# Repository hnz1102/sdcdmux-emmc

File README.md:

<div align="center">
  <h1><code>SDCDMUX</code></h1>
  
</div>

# SDCDMUX : SD Card and eMMC Device Multiplexsor with Infrared Remote Control

The SDCDMUX provides a convenient and quick change of a SW image of a device that has an SD Card interface from a remote. 

When I am developing by booting from an SD memory card on a device such as the Raspberry Pi, it is not easy to rewrite the SD card image and replace it by hand. Remove the SD card, insert it into the host PC, and take a dozen minutes rewriting the SW image, after that, return the SD card to the device and turn on the power... But, This tool can change the image of the eMMC directly from the host PC, and the device can be booted as an SD card with the new image.

Usually, To boot with the new SW image, the device must be reset, but this tool can learn the ON/OFF command of the infrared power controller and outputs that command to turn the device on and off.

This tool frees me from the tedious SW image rewriting and resetting process.

https://github.com/hnz1102/sdcdmux-emmc/assets/111413646/edf4297e-6da3-4eba-aacd-01ee126e1040

### [2023.8.15] USB Type-C version Added.

The Schematic is hardware/emmc-type-c-version/ directory.

## Features

- **Fast**. SDCDMUX can write an image to the eMMC device (32GB) instead of SD Memory Card via High-Speed USB. It is 4 times faster than an SD card. 

- **Remote Control**. SDCDMUX has an infrared interface that can receive an infrared remote control command and send it to power control devices. If you want to turn on a device, you can type the command "on" on the PC console.

- **Use Fast Switch**. When I used the prototype, Sometimes Rasbery Pi4 could not boot by read error. I tried to change faster switching devices in this tool. Then, Raspberry Pi always can boot correctly.

## Tested Devices

I have checked the following devices that can boot from this tool.

- [Raspberry Pi 4 Model B](https://www.raspberrypi.com/products/raspberry-pi-4-model-b/)
- [BeagleBone Black](https://beagleboard.org/black)
- [BeagleBone Blue](https://beagleboard.org/blue)

Only 3 devices because I have my own now.

## Infrared Remote Power Switch

The Infrared Remote Contorol Power Swtich I used is [OCR-05W OHM ELECTRIC INC.](https://www.ohm-electric.co.jp/product/c23/c2313/19582/). But I think other switch devices that can control by the infrared LED may be able to work too. 

## How to build the control SW.

This software (sdcdmux) is for Linux. 

The following example is for Ubuntu Linux Ubuntu 22.04.2 LTS.

1. Install build tools
```
$ sudo apt -y install build-essential libftdi-dev
```

2. Build the software.
```
$ cd sdcdmux
$ make
$ sudo cp sdcdmux /usr/local/bin/ 
```
3. Add a udev rule.
/etc/udev/rules.d/99-ft232h.rules
```
$ sudo su
# echo 'SUBSYSTEMS=="usb", ATTRS{idVendor}=="0403", ATTRS{idProduct}=="6014",  MODE=
"0666"' > /etc/udev/rules.d/99-ft232h.rules
# udevadm control --reload-rules
# udevadm trigger
```

## How to use SDCDMUX.

1. Connect to SDCDMUX via the USB cable with your PC. Power USB cable connect to the target device and USB adoptor. Please refer to the figure. 

2. Use SDCDMUX

- Display current status.
```
$ sdcdmux
Memory Device is connected to : HOST.
```

- Capture infrared ON command.
```
$ sdcdmux -c on
Capture Start.. 
"Push ON button on your Infrared Remote Controller"
Recieve IFR data (18245B)
Captured command for on
```

After capture the command, you can see the 'if-on' file in the current directory.

- Capture infrared OFF command.
```
$ sdcdmux -c off
Capture Start.. 
"Push OFF button on your Infrared Remote Controller"
Recieve IFR data (11449B)
Captured command for off
```

- Select eMMC memory to host PC side.
```
$ sdcdmux -s host
Memory Device is connected to : HOST.
```
You can see eMMC disk drive on your PC.
```
$ lsblk
:
sdb           8:16   1  29.1G  0 disk 
:
```
In my case, I can see the new disk drive as 'sdb'.

- Download the Raspberry Pi boot image and Write it to eMMC.

** !WARNING! ** DO NOT OVERWRITE YOUR SYSTEM DISK DRIVE! BE CAREFUL THE WRITING DISK DRIVE NAME.

```
$ wget https://downloads.raspberrypi.org/raspios_armhf/images/raspios_armhf-2023-05-03/2023-05-03-raspios-bullseye-armhf.img.xz
$ xzcat 2023-05-03-raspios-bullseye-armhf.img.xz | sudo dd of=/dev/sdb bs=1M status=progress
4125163520 bytes (4.1 GB, 3.8 GiB) copied, 94 s, 43.9 MB/s
0+491118 records in
0+491118 records out
4143972352 bytes (4.1 GB, 3.9 GiB) copied, 126.121 s, 32.9 MB/s
$ lsblk
sdb           8:16   1  29.1G  0 disk 
├─sdb1        8:17   1   256M  0 part 
└─sdb2        8:18   1   3.6G  0 part 
```

- Select eMMC memory to target (Raspberry Pi) device.
```
$ sdcdmux -s target
Memory Device is connected to : TARGET.
```
You can see the blue LED is turn on.

- Turn on the device using infrared on command.
```
$ sdcdmux -x on
```

- Turn off the device using infrared on command.
```
$ sdcdmux -x off
```

- Another devices control.

I also use the SDCDMUX as a controller to turn ceiling lights on and off.
```
$ sdcdmux -c lightson
Capture Start.. 
"Press ON on the remote controller of the ceiling light to make it learn the command."
Recieve IFR data (8498B)
Captured command for lightson

$ sdcdmux -c lightsoff
Capture Start.. 
"Press OFF on the remote controller of the ceiling light to make it learn the command."
Recieve IFR data (10701B)
Captured command for lightsoff

$ sdcdmux -x lightson
"Seiling lights turn on."

$ sdcdmux -x lightsoff
"Seiling lights turn off."
```

## Performance

I created an SD card type and an eMMC type. I compared their writing times.

4.2GB Image Writing Time (Average of 3 times)
|SD card (*1)|eMMC (*2)|
|----|----|
|482.3 sec (8.7MB/s)|134.7 sec (31.3MB/s)|

*1 San Disk Ultla 32GB HC1 SD CARD

*2 Delkin Devices EM32VSUKN 32GB eMMC

## SDCDMUX Board

SDCDMUX Board Schematic and a PCB layout are placed in the hardware directory. There are 2 types emmc-version and sdcard-version. This emmc-version uses an eMMC device instead of a SD memory card.
Schematic data is created by KidCad 7.0.

If you order a PCB board from a PCB maker, it must be 0.8mm thick. Otherwise, it will not fit in the SD card slot.

After building the board, It has to configure EEPROMs of the USB Media Controller and USB FIFO Interface.

The USB Media Controller has an EEPROM. It is programmed with the parameters by [USBDM tool](https://www.microchip.com/en-us/software-library/usbdm-tool).

- Manufacture String
- Serial Number String

Single Channel HiSpeed USB to Multipurpose UART/FIFO IC (FT232H) has an EEPROM too. It is programmed the parameters by [FT_Prog](https://ftdichip.com/wp-content/uploads/2023/06/FT_Prog_v3.12.32.640-Installer.zip).

- FT EEPROM - HARDWARE Specific IO Controls - C5, C6, C8 and C9 ports are I/O Mode set.

# CASE

I created the case for SDCDMUX type-C version by 3D printer. There are STL data in the hardware/emmc-type-c-version/case directory.

## LICENSE
This Software is licensed under MIT. Other Hardware Schematic documents are licensed under CC-BY-SA V4.0.

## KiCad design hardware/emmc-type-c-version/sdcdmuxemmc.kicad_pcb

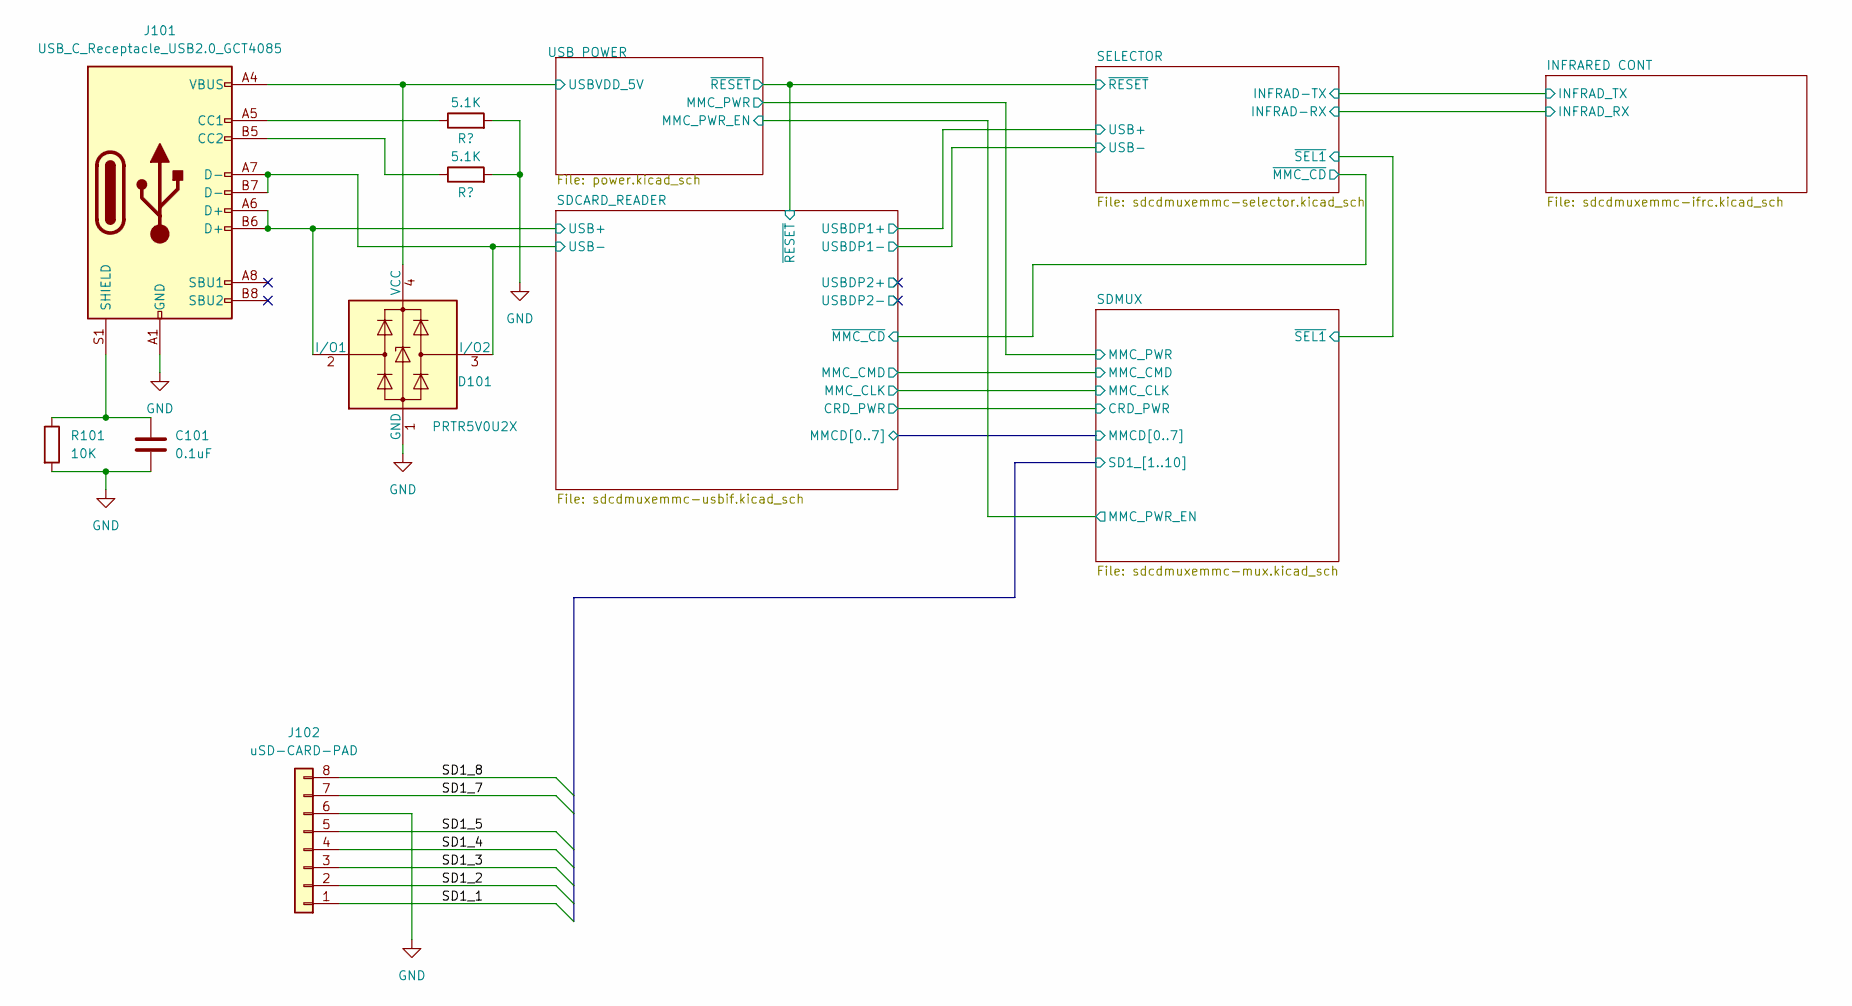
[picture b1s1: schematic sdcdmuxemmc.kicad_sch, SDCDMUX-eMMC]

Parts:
C101: 0.1uF; C_0603_1608Metric_Pad1.08x0.95mm_HandSolder; digikey 311-1824-1-ND
D101: PRTR5V0U2X; SOT-143; digikey 1727-3884-1-ND
J101: USB_C_Receptacle_USB2.0_GCT4085; USB_C_Receptacle_GCT_USB4085; digikey 2073-USB4085-GF-ACT-ND
J102: uSD-CARD-PAD; uSD Card Pad
R101: 10K; R_0805_2012Metric_Pad1.20x1.40mm_HandSolder; digikey 13-RC0603JR-1010KLCT-ND
R102, R103: 5.1K; R_0805_2012Metric_Pad1.20x1.40mm_HandSolder; digikey 13-RC0603JR-1010KLCT-ND

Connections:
/SDCARD_READER/USB+: D101.2 (I/O1), J101.A6 (D+), J101.B6 (D+); also elsewhere on the board
/SDCARD_READER/USB-: D101.3 (I/O2), J101.A7 (D-), J101.B7 (D-); also elsewhere on the board
/SDMUX/SD1_1: J102.1; also elsewhere on the board
/SDMUX/SD1_2: J102.2; also elsewhere on the board
/SDMUX/SD1_3: J102.3; also elsewhere on the board
/SDMUX/SD1_4: J102.4; also elsewhere on the board
/SDMUX/SD1_5: J102.5; also elsewhere on the board
/SDMUX/SD1_7: J102.7; also elsewhere on the board
/SDMUX/SD1_8: J102.8; also elsewhere on the board
/USB POWER/USBVDD_5V: D101.4 (VCC), J101.A4 (VBUS), J101.A9 (VBUS), J101.B4 (VBUS), J101.B9 (VBUS); also elsewhere on the board
GND: C101.2, D101.1 (GND), J101.A1 (GND), J101.A12 (GND), J101.B1 (GND), J101.B12 (GND), J102.6, R101.2, R102.2, R103.2; also elsewhere on the board
unnamed: J101.A5 (CC1), R102.1
unnamed: J101.B5 (CC2), R103.1
unnamed: C101.1, J101.S1 (SHIELD), R101.1

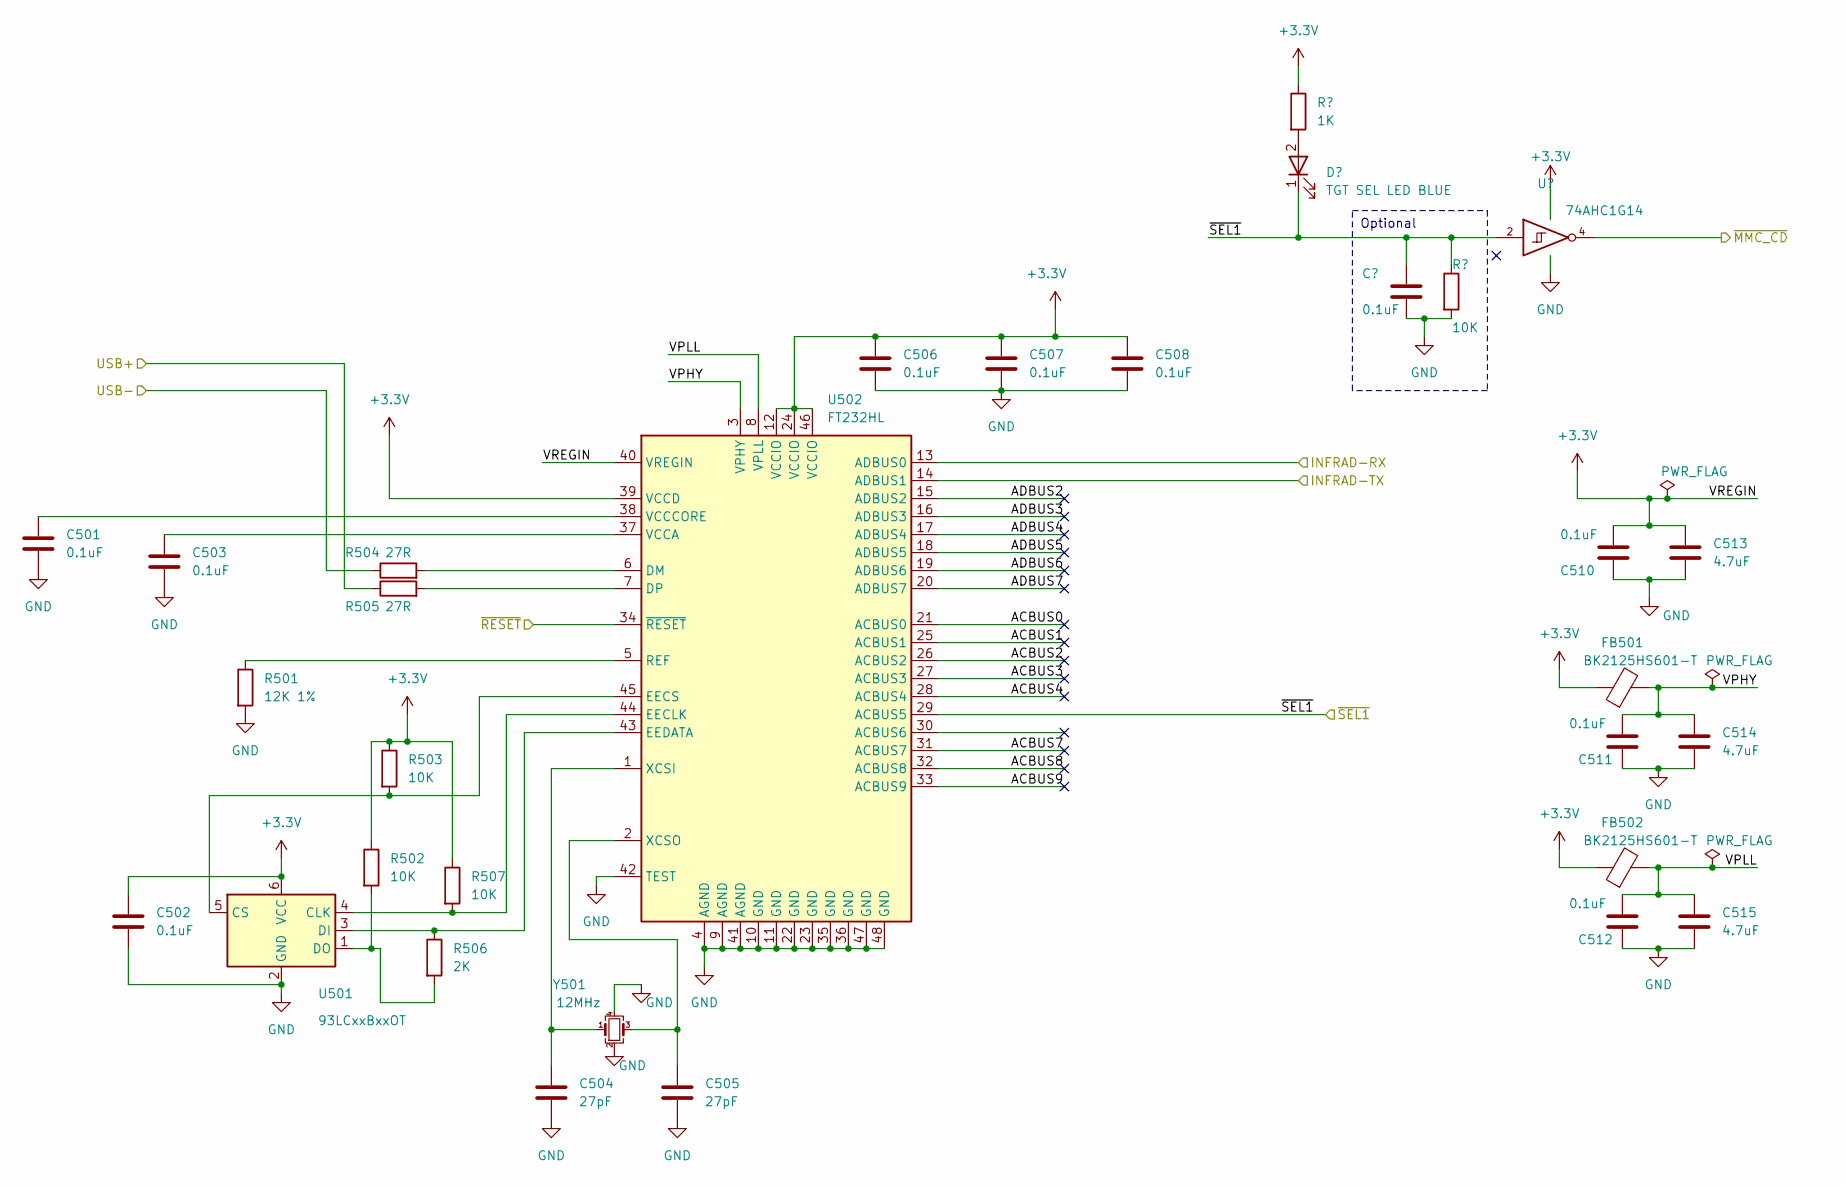
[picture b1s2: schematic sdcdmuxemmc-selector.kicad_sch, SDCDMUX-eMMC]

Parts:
C501, C502, C503, C506, C507, C508, C509, C510, C511, C512: 0.1uF; C_0603_1608Metric_Pad1.08x0.95mm_HandSolder; digikey 311-1824-1-ND
C504, C505: 27pF; C_0603_1608Metric_Pad1.08x0.95mm_HandSolder; digikey 311-1063-1-ND
C513, C514, C515: 4.7uF; C_0805_2012Metric_Pad1.18x1.45mm_HandSolder; digikey 311-1455-1-ND
D501: TGT SEL LED BLUE; LED_0603_1608Metric_Pad1.05x0.95mm_HandSolder; digikey 846-1177-1-ND
FB501, FB502: BK2125HS601-T; L_0805_2012Metric_Pad1.15x1.40mm_HandSolder; digikey 240-2399-1-ND
R501: 12K 1%; R_0805_2012Metric_Pad1.20x1.40mm_HandSolder; digikey 311-12.0KHRCT-ND
R502, R503, R507, R509: 10K; R_0805_2012Metric_Pad1.20x1.40mm_HandSolder; digikey 13-RC0603JR-1010KLCT-ND
R504, R505: 27R; R_0603_1608Metric_Pad0.98x0.95mm_HandSolder; digikey 311-27GRCT-ND
R506: 2K; R_0805_2012Metric_Pad1.20x1.40mm_HandSolder; digikey 311-2.0KGRCT-ND
R508: 1K; R_0805_2012Metric_Pad1.20x1.40mm_HandSolder; digikey 13-RC0603JR-101KLCT-ND
U501: 93LCxxBxxOT; SOT-23-6; digikey 93LC56BT-I/OTCT-ND
U502: FT232HL; LQFP-48_7x7mm_P0.5mm; digikey 768-1348-ND
U503: 74AHC1G14; SOT-23-5_HandSoldering; digikey 74AHC1G14W5-7DICT-ND
Y501: 12MHz; Crystal_SMD_3225-4Pin_3.2x2.5mm; digikey SER3682CT-ND

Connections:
+3.3V: C502.1, C506.1, C507.1, C508.1, C510.1, C513.1, FB501.1, FB502.1, R502.1, R503.1, R507.1, R508.1, U501.6 (VCC), U502.12 (VCCIO), U502.24 (VCCIO), U502.39 (VCCD), U502.40 (VREGIN), U502.46 (VCCIO), U503.5 (VCC); also elsewhere on the board
/INFRARED CONT/INFRAD_RX: U502.13 (ADBUS0); also elsewhere on the board
/INFRARED CONT/INFRAD_TX: U502.14 (ADBUS1); also elsewhere on the board
/SDCARD_READER/USBDP1+: R505.1; also elsewhere on the board
/SDCARD_READER/USBDP1-: R504.1; also elsewhere on the board
/SDCARD_READER/~MMC_CD: U503.4; also elsewhere on the board
/SDCARD_READER/~RESET: U502.34 (~RESET); also elsewhere on the board
/SELECTOR/ACBUS0: U502.21 (ACBUS0)
/SELECTOR/ACBUS1: U502.25 (ACBUS1)
/SELECTOR/ACBUS2: U502.26 (ACBUS2)
/SELECTOR/ACBUS3: U502.27 (ACBUS3)
/SELECTOR/ACBUS4: U502.28 (ACBUS4)
/SELECTOR/ACBUS7: U502.31 (ACBUS7)
/SELECTOR/ACBUS8: U502.32 (ACBUS8)
/SELECTOR/ACBUS9: U502.33 (ACBUS9)
/SELECTOR/ADBUS2: U502.15 (ADBUS2)
/SELECTOR/ADBUS3: U502.16 (ADBUS3)
/SELECTOR/ADBUS4: U502.17 (ADBUS4)
/SELECTOR/ADBUS5: U502.18 (ADBUS5)
/SELECTOR/ADBUS6: U502.19 (ADBUS6)
/SELECTOR/ADBUS7: U502.20 (ADBUS7)
/SELECTOR/VPHY: C511.1, C514.1, FB501.2, U502.3 (VPHY)
/SELECTOR/VPLL: C512.1, C515.1, FB502.2, U502.8 (VPLL)
/SELECTOR/~SEL1: C509.1, D501.1 (K), R509.1, U502.29 (ACBUS5), U503.2; also elsewhere on the board
GND: C501.2, C502.2, C503.2, C504.2, C505.2, C506.2, C507.2, C508.2, C509.2, C510.2, C511.2, C512.2, C513.2, C514.2, C515.2, R501.2, R509.2, U501.2 (GND), U502.4 (AGND), U502.9 (AGND), U502.10 (GND), U502.11 (GND), U502.22 (GND), U502.23 (GND), U502.35 (GND), U502.36 (GND), U502.41 (AGND), U502.42 (TEST), U502.47 (GND), U502.48 (GND), U503.3 (GND), Y501.2, Y501.4; also elsewhere on the board
unnamed: D501.2 (A), R508.2
unnamed: R507.2, U501.4 (CLK), U502.44 (EECLK)
unnamed: R503.2, U501.5 (CS), U502.45 (EECS)
unnamed: R506.1, U501.3 (DI), U502.43 (EEDATA)
unnamed: R502.2, R506.2, U501.1 (DO)
unnamed: R504.2, U502.6 (DM)
unnamed: R505.2, U502.7 (DP)
unnamed: R501.1, U502.5 (REF)
unnamed: C503.1, U502.37 (VCCA)
unnamed: C501.1, U502.38 (VCCCORE)
unnamed: C504.1, U502.1 (XCSI), Y501.1
unnamed: C505.1, U502.2 (XCSO), Y501.3

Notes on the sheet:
Optional

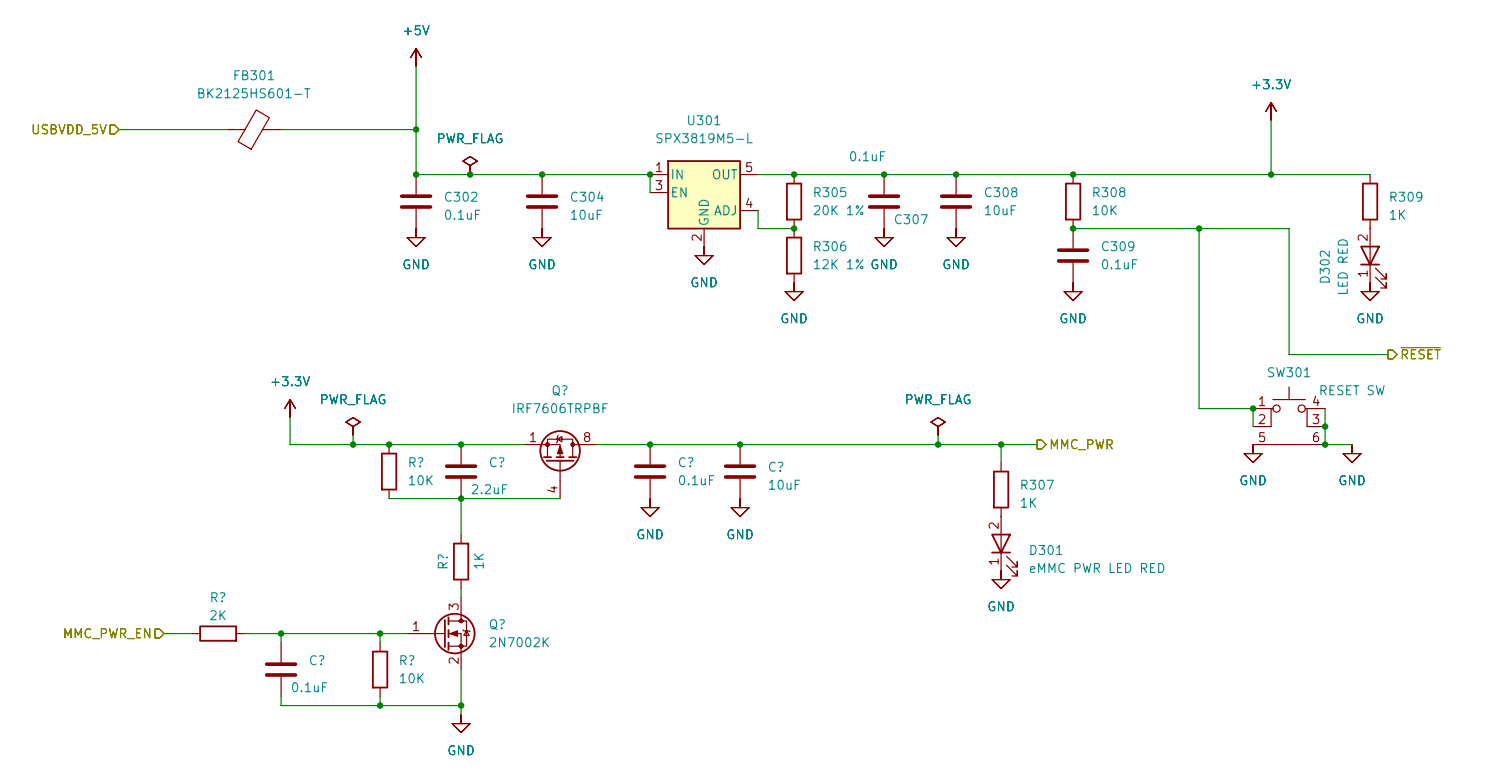
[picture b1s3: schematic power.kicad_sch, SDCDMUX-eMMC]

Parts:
C301, C302, C305, C307, C309: 0.1uF; C_0603_1608Metric_Pad1.08x0.95mm_HandSolder; digikey 311-1824-1-ND
C303: 2.2uF; C_0603_1608Metric_Pad1.08x0.95mm_HandSolder; digikey 311-1795-1-ND
C304, C306, C308: 10uF; C_0805_2012Metric_Pad1.18x1.45mm_HandSolder; digikey 311-3494-1-ND
D301: eMMC PWR LED RED; LED_0603_1608Metric_Pad1.05x0.95mm_HandSolder; digikey 511-1587-1-ND
D302: LED RED; LED_0603_1608Metric_Pad1.05x0.95mm_HandSolder; digikey 511-1587-1-ND
FB301: BK2125HS601-T; L_0603_1608Metric_Pad1.05x0.95mm_HandSolder; digikey 240-2399-1-ND
Q301: 2N7002K; SOT-23; digikey 2N7002K-7DICT-ND
Q302: IRF7606TRPBF; MSOP-8_3x3mm_P0.65mm; digikey IRF7606TRPBFCT-ND
R301: 2K; R_0805_2012Metric_Pad1.20x1.40mm_HandSolder; digikey 311-2.0KGRCT-ND
R302, R303, R308: 10K; R_0805_2012Metric_Pad1.20x1.40mm_HandSolder; digikey 13-RC0603JR-1010KLCT-ND
R304, R307, R309: 1K; R_0805_2012Metric_Pad1.20x1.40mm_HandSolder; digikey 13-RC0603JR-101KLCT-ND
R305: 20K 1%; R_0805_2012Metric_Pad1.20x1.40mm_HandSolder; digikey 13-RC0603FR-1320KLCT-ND
R306: 12K 1%; R_0805_2012Metric_Pad1.20x1.40mm_HandSolder; digikey 311-12.0KHRCT-ND
SW301: RESET SW; WS-TASV SMT Tact Switch; digikey 732-435151014824CT-ND
U301: SPX3819M5-L; SOT-23-5; digikey 1016-1871-1-ND

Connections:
+3.3V: C303.1, C307.1, C308.1, Q302.1 (S), Q302.2 (S), Q302.3 (S), R303.1, R305.1, R308.1, R309.1, U301.5 (OUT); also elsewhere on the board
+5V: C302.1, C304.1, FB301.2, U301.1 (IN), U301.3 (EN); also elsewhere on the board
/SDCARD_READER/~RESET: C309.1, R308.2, SW301.1, SW301.2; also elsewhere on the board
/SDMUX/MMC_PWR: C305.1, C306.1, Q302.5 (D), Q302.6 (D), Q302.7 (D), Q302.8 (D), R307.1; also elsewhere on the board
/SDMUX/MMC_PWR_EN: R301.1; also elsewhere on the board
/USB POWER/USBVDD_5V: FB301.1; also elsewhere on the board
GND: C301.2, C302.2, C304.2, C305.2, C306.2, C307.2, C308.2, C309.2, D301.1 (K), D302.1 (K), Q301.2 (S), R302.2, R306.2, SW301.3 (K), SW301.4 (A), SW301.5, SW301.6, U301.2 (GND); also elsewhere on the board
unnamed: D301.2 (A), R307.2
unnamed: D302.2 (A), R309.2
unnamed: Q301.3 (D), R304.1
unnamed: C301.1, Q301.1 (G), R301.2, R302.1
unnamed: C303.2, Q302.4 (G), R303.2, R304.2
unnamed: R305.2, R306.1, U301.4 (ADJ)

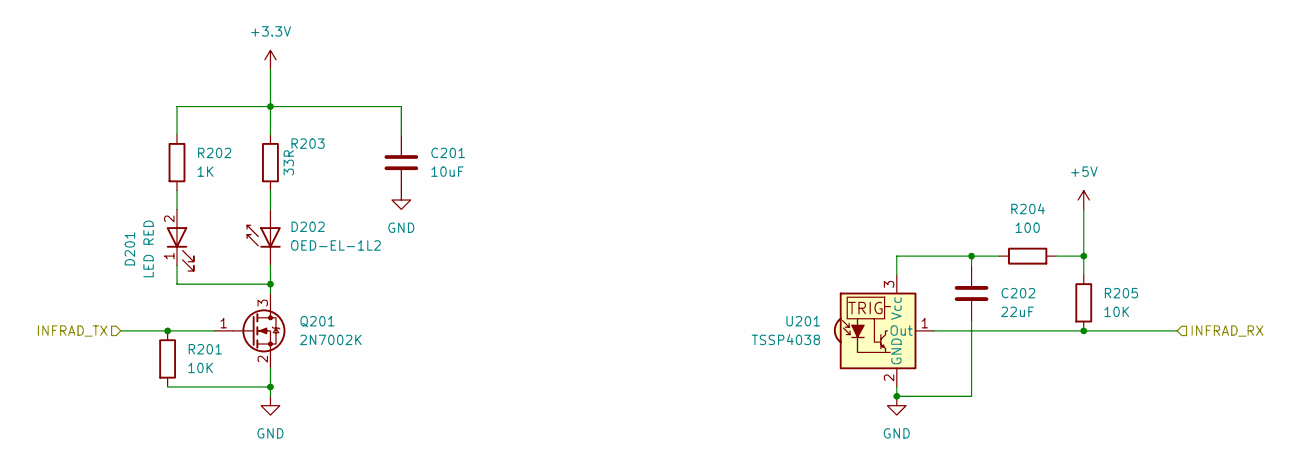
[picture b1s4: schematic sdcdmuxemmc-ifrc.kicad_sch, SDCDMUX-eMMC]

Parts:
C201: 10uF; C_0805_2012Metric_Pad1.18x1.45mm_HandSolder; digikey 311-3494-1-ND
C202: 22uF; C_0805_2012Metric_Pad1.18x1.45mm_HandSolder; digikey 311-3494-1-ND
D201: LED RED; LED_0603_1608Metric_Pad1.05x0.95mm_HandSolder; digikey 511-1587-1-ND
D202: OED-EL-1L2; LED_D5.0mm; digikey 67-1001-ND
Q201: 2N7002K; SOT-23; digikey 2N7002K-7DICT-ND
R201, R205: 10K; R_0805_2012Metric_Pad1.20x1.40mm_HandSolder; digikey 13-RC0603JR-1010KLCT-ND
R202: 1K; R_0805_2012Metric_Pad1.20x1.40mm_HandSolder; digikey 13-RC0603JR-101KLCT-ND
R203: 33R; R_0603_1608Metric_Pad0.98x0.95mm_HandSolder; digikey 311-33GRCT-ND
R204: 100; R_0805_2012Metric_Pad1.20x1.40mm_HandSolder; digikey 13-RC0603JR-1010KLCT-ND
U201: TSSP4038; digikey TSSP4038-ND

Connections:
+3.3V: C201.1, R202.1, R203.1; also elsewhere on the board
+5V: R204.2, R205.1; also elsewhere on the board
/INFRARED CONT/INFRAD_RX: R205.2, U201.1 (Out); also elsewhere on the board
/INFRARED CONT/INFRAD_TX: Q201.1 (G), R201.1; also elsewhere on the board
GND: C201.2, C202.2, Q201.2 (S), R201.2, U201.2 (GND); also elsewhere on the board
unnamed: D201.2 (A), R202.2
unnamed: D201.1 (K), D202.1 (K), Q201.3 (D)
unnamed: D202.2 (A), R203.2
unnamed: C202.1, R204.1, U201.3 (Vcc)

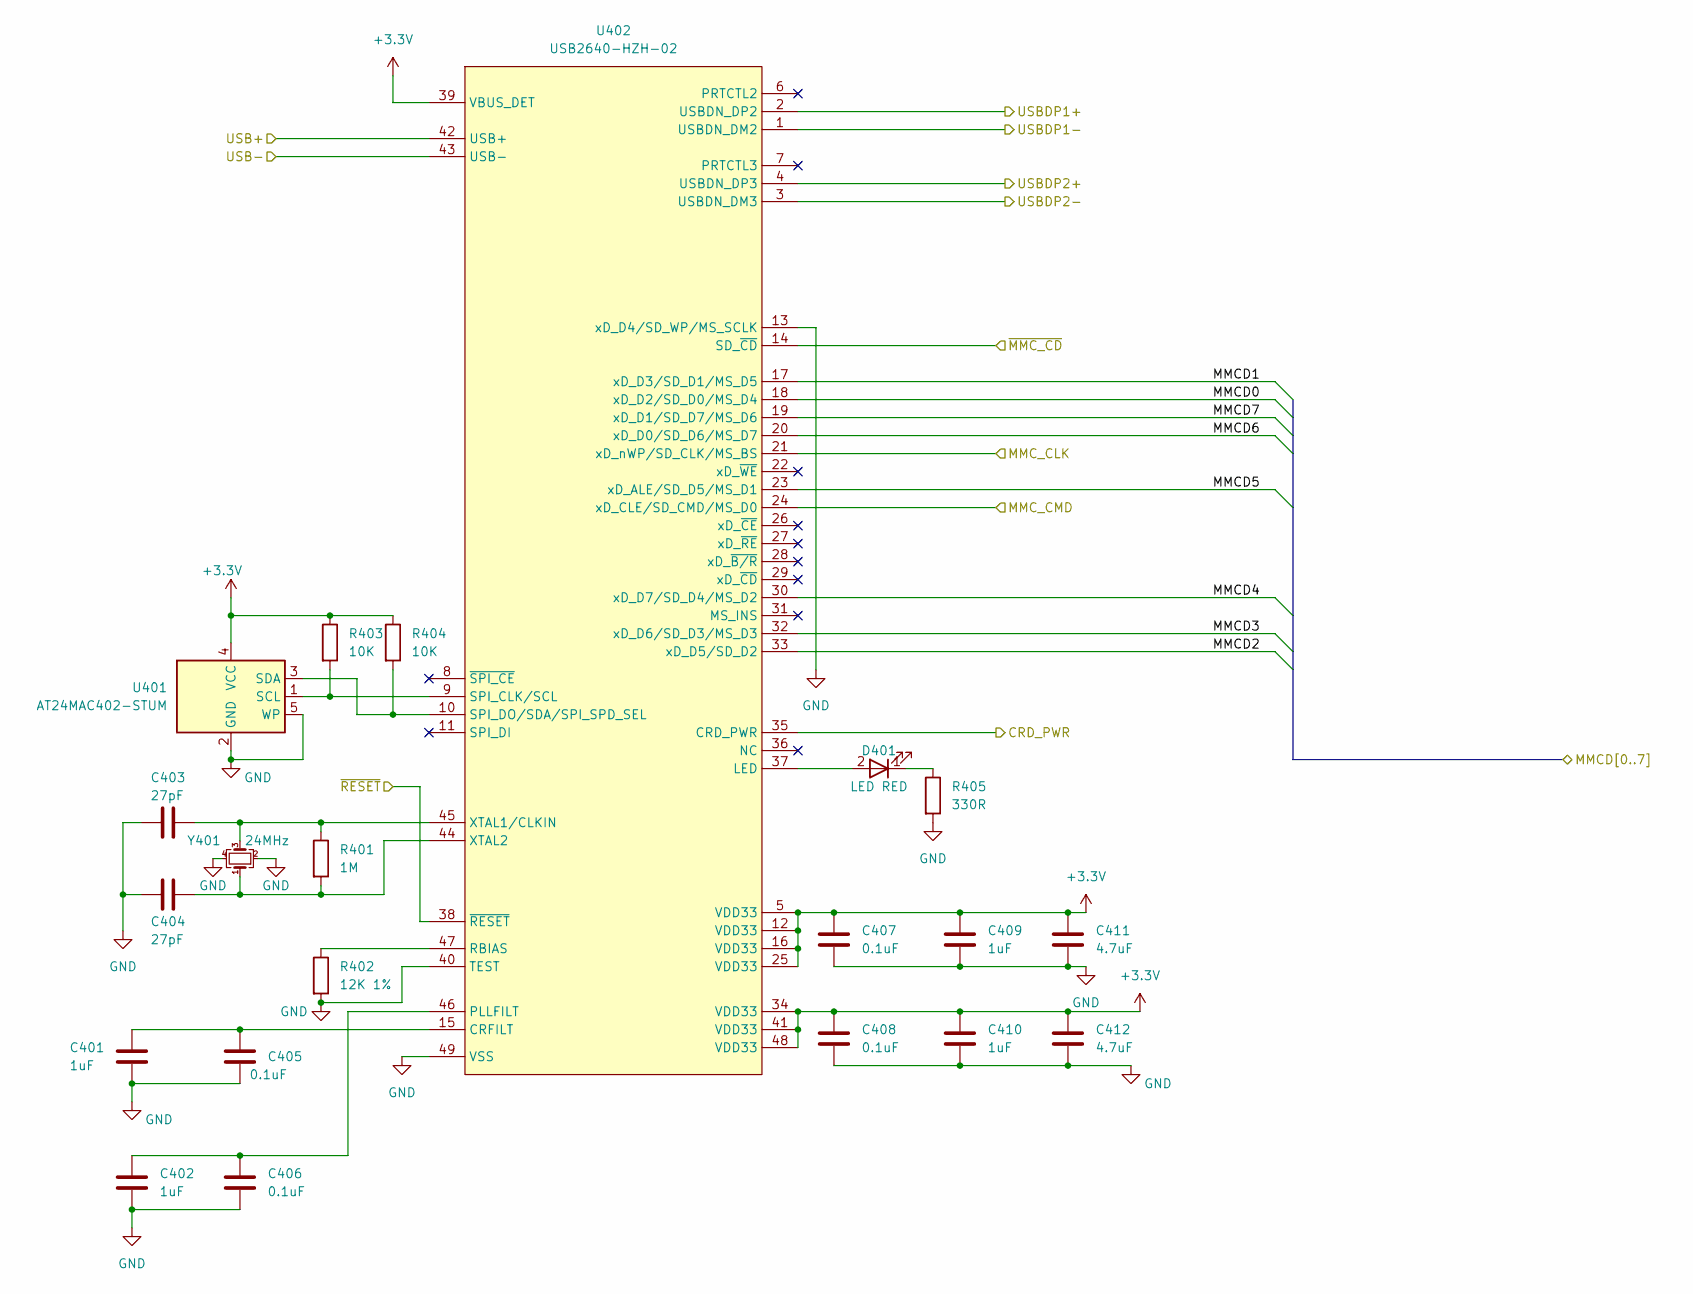
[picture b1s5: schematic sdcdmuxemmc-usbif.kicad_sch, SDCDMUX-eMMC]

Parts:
C401, C402, C409, C410: 1uF; C_0805_2012Metric_Pad1.18x1.45mm_HandSolder; digikey 13-CC0603KPX7R7BB105CT-ND
C403, C404: 27pF; C_0603_1608Metric; digikey 311-1063-1-ND
C405, C406, C407, C408: 0.1uF; C_0603_1608Metric_Pad1.08x0.95mm_HandSolder; digikey 311-1824-1-ND
C411, C412: 4.7uF; C_0805_2012Metric_Pad1.18x1.45mm_HandSolder; digikey 311-1455-1-ND
D401: LED RED; LED_0603_1608Metric_Pad1.05x0.95mm_HandSolder; digikey 511-1587-1-ND
R401: 1M; R_0805_2012Metric_Pad1.20x1.40mm_HandSolder; digikey 311-1.0MGRCT-ND
R402: 12K 1%; R_0805_2012Metric_Pad1.20x1.40mm_HandSolder; digikey 311-12.0KHRCT-ND
R403, R404: 10K; R_0805_2012Metric_Pad1.20x1.40mm_HandSolder; digikey 13-RC0603JR-1010KLCT-ND
R405: 330R; R_0805_2012Metric_Pad1.20x1.40mm_HandSolder; digikey 311-330GRCT-ND
U401: AT24MAC402-STUM; SOT-23-5_HandSoldering; digikey AT24MAC402-STUM-TCT-ND
U402: USB2640-HZH-02; QFN-48-1EP_7x7mm_P0.5mm_EP5.15x5.15mm; digikey USB2640-HZH-02-ND
Y401: 24MHz; Crystal_SMD_2016-4Pin_2.0x1.6mm; digikey XC3064CT-ND

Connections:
+3.3V: C407.1, C408.1, C409.1, C410.1, C411.1, C412.1, R403.1, R404.1, U401.4 (VCC), U402.5 (VDD33), U402.12 (VDD33), U402.16 (VDD33), U402.25 (VDD33), U402.34 (VDD33), U402.39 (VBUS_DET), U402.41 (VDD33), U402.48 (VDD33); also elsewhere on the board
/SDCARD_READER/CRD_PWR: U402.35 (CRD_PWR); also elsewhere on the board
/SDCARD_READER/MMCD0: U402.18 (xD_D2/SD_D0/MS_D4); also elsewhere on the board
/SDCARD_READER/MMCD1: U402.17 (xD_D3/SD_D1/MS_D5); also elsewhere on the board
/SDCARD_READER/MMCD2: U402.33 (xD_D5/SD_D2); also elsewhere on the board
/SDCARD_READER/MMCD3: U402.32 (xD_D6/SD_D3/MS_D3); also elsewhere on the board
/SDCARD_READER/MMCD4: U402.30 (xD_D7/SD_D4/MS_D2); also elsewhere on the board
/SDCARD_READER/MMCD5: U402.23 (xD_ALE/SD_D5/MS_D1); also elsewhere on the board
/SDCARD_READER/MMCD6: U402.20 (xD_D0/SD_D6/MS_D7); also elsewhere on the board
/SDCARD_READER/MMCD7: U402.19 (xD_D1/SD_D7/MS_D6); also elsewhere on the board
/SDCARD_READER/MMC_CLK: U402.21 (xD_nWP/SD_CLK/MS_BS); also elsewhere on the board
/SDCARD_READER/MMC_CMD: U402.24 (xD_CLE/SD_CMD/MS_D0); also elsewhere on the board
/SDCARD_READER/USB+: U402.42 (USB+); also elsewhere on the board
/SDCARD_READER/USB-: U402.43 (USB-); also elsewhere on the board
/SDCARD_READER/USBDP1+: U402.2 (USBDN_DP2); also elsewhere on the board
/SDCARD_READER/USBDP1-: U402.1 (USBDN_DM2); also elsewhere on the board
/SDCARD_READER/USBDP2+: U402.4 (USBDN_DP3)
/SDCARD_READER/USBDP2-: U402.3 (USBDN_DM3)
/SDCARD_READER/~MMC_CD: U402.14 (SD_~CD); also elsewhere on the board
/SDCARD_READER/~RESET: U402.38 (~RESET); also elsewhere on the board
GND: C401.2, C402.2, C403.1, C404.1, C405.2, C406.2, C407.2, C408.2, C409.2, C410.2, C411.2, C412.2, R402.2, R405.2, U401.2 (GND), U401.5 (WP), U402.13 (xD_D4/SD_WP/MS_SCLK), U402.40 (TEST), U402.49 (VSS), Y401.2, Y401.4; also elsewhere on the board
unnamed: D401.2 (A), U402.37 (LED)
unnamed: D401.1 (K), R405.1
unnamed: R403.2, U401.1 (SCL), U402.9 (SPI_CLK/SCL)
unnamed: R404.2, U401.3 (SDA), U402.10 (SPI_DO/SDA/SPI_SPD_SEL)
unnamed: C401.1, C405.1, U402.15 (CRFILT)
unnamed: C402.1, C406.1, U402.46 (PLLFILT)
unnamed: R402.1, U402.47 (RBIAS)
unnamed: C403.2, R401.1, U402.45 (XTAL1/CLKIN), Y401.3
unnamed: C404.2, R401.2, U402.44 (XTAL2), Y401.1

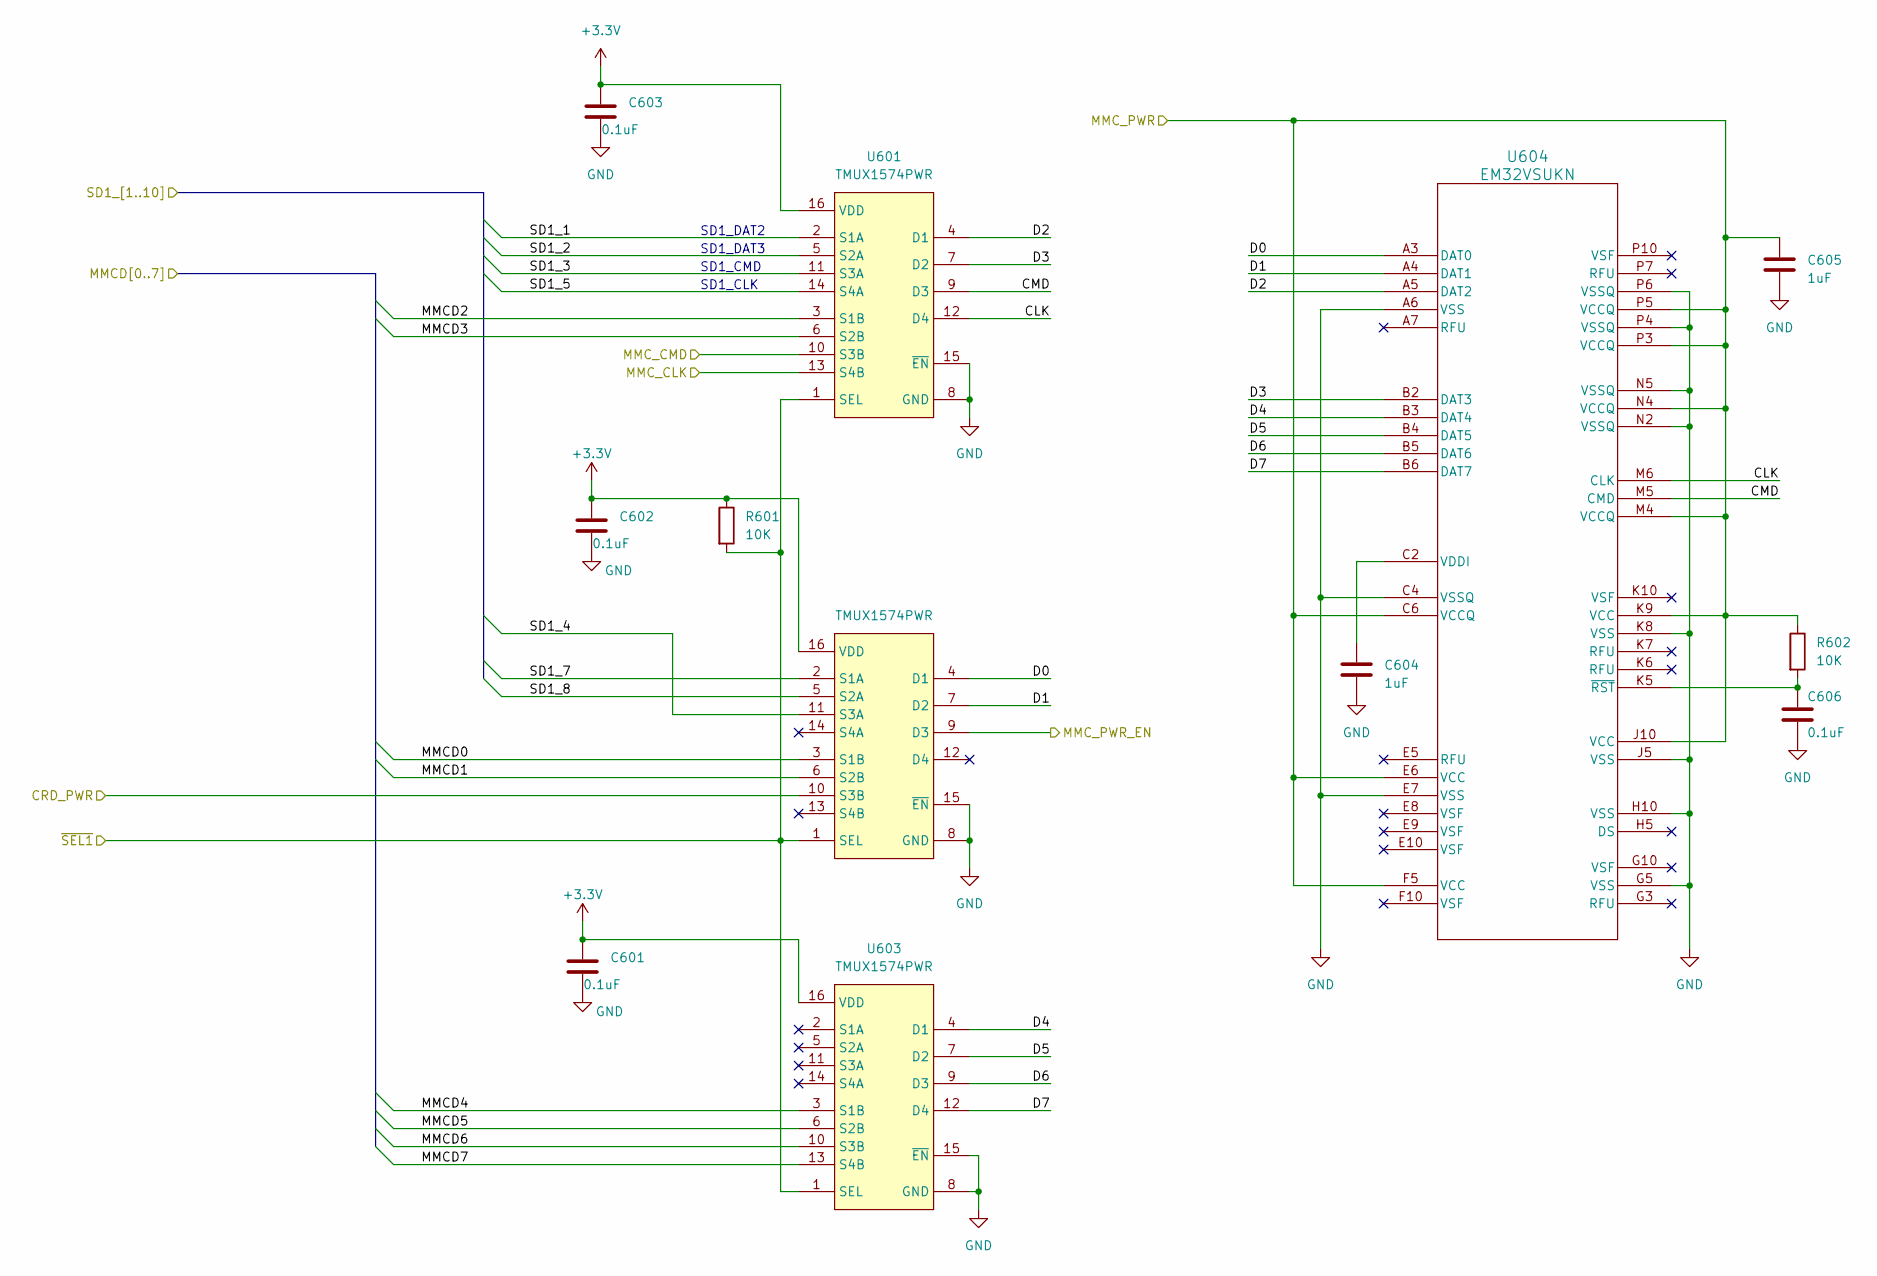
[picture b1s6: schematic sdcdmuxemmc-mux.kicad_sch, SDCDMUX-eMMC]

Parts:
C601, C602, C603, C606: 0.1uF; C_0603_1608Metric_Pad1.08x0.95mm_HandSolder; digikey 311-1824-1-ND
C604, C605: 1uF; C_0805_2012Metric; digikey 13-CC0603KPX7R7BB105CT-ND
R601, R602: 10K; R_0805_2012Metric_Pad1.20x1.40mm_HandSolder; digikey 13-RC0603JR-1010KLCT-ND
U601, U602, U603: TMUX1574PWR; TSSOP-16_4.4x5mm_P0.65mm; digikey 296-53444-1-ND
U604: EM32VSUKN; EM32VSUKN FPGA153; digikey 3247-EM32VSUKN-BA000-2-ND

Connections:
+3.3V: C601.1, C602.1, C603.1, R601.1, U601.16 (VDD), U602.16 (VDD), U603.16 (VDD); also elsewhere on the board
/SDCARD_READER/CRD_PWR: U602.10 (S3B); also elsewhere on the board
/SDCARD_READER/MMCD0: U602.3 (S1B); also elsewhere on the board
/SDCARD_READER/MMCD1: U602.6 (S2B); also elsewhere on the board
/SDCARD_READER/MMCD2: U601.3 (S1B); also elsewhere on the board
/SDCARD_READER/MMCD3: U601.6 (S2B); also elsewhere on the board
/SDCARD_READER/MMCD4: U603.3 (S1B); also elsewhere on the board
/SDCARD_READER/MMCD5: U603.6 (S2B); also elsewhere on the board
/SDCARD_READER/MMCD6: U603.10 (S3B); also elsewhere on the board
/SDCARD_READER/MMCD7: U603.13 (S4B); also elsewhere on the board
/SDCARD_READER/MMC_CLK: U601.13 (S4B); also elsewhere on the board
/SDCARD_READER/MMC_CMD: U601.10 (S3B); also elsewhere on the board
/SDMUX/CLK: U601.12 (D4), U604.M6 (CLK)
/SDMUX/CMD: U601.9 (D3), U604.M5 (CMD)
/SDMUX/D0: U602.4 (D1), U604.A3 (DAT0)
/SDMUX/D1: U602.7 (D2), U604.A4 (DAT1)
/SDMUX/D2: U601.4 (D1), U604.A5 (DAT2)
/SDMUX/D3: U601.7 (D2), U604.B2 (DAT3)
/SDMUX/D4: U603.4 (D1), U604.B3 (DAT4)
/SDMUX/D5: U603.7 (D2), U604.B4 (DAT5)
/SDMUX/D6: U603.9 (D3), U604.B5 (DAT6)
/SDMUX/D7: U603.12 (D4), U604.B6 (DAT7)
/SDMUX/MMC_PWR: C605.1, R602.1, U604.C6 (VCCQ), U604.E6 (VCC), U604.F5 (VCC), U604.J10 (VCC), U604.K9 (VCC), U604.M4 (VCCQ), U604.N4 (VCCQ), U604.P3 (VCCQ), U604.P5 (VCCQ); also elsewhere on the board
/SDMUX/MMC_PWR_EN: U602.9 (D3); also elsewhere on the board
/SDMUX/SD1_1: U601.2 (S1A); also elsewhere on the board
/SDMUX/SD1_2: U601.5 (S2A); also elsewhere on the board
/SDMUX/SD1_3: U601.11 (S3A); also elsewhere on the board
/SDMUX/SD1_4: U602.11 (S3A); also elsewhere on the board
/SDMUX/SD1_5: U601.14 (S4A); also elsewhere on the board
/SDMUX/SD1_7: U602.2 (S1A); also elsewhere on the board
/SDMUX/SD1_8: U602.5 (S2A); also elsewhere on the board
/SELECTOR/~SEL1: R601.2, U601.1 (SEL), U602.1 (SEL), U603.1 (SEL); also elsewhere on the board
GND: C601.2, C602.2, C603.2, C604.2, C605.2, C606.2, U601.8 (GND), U601.15 (~EN), U602.8 (GND), U602.15 (~EN), U603.8 (GND), U603.15 (~EN), U604.A6 (VSS), U604.C4 (VSSQ), U604.E7 (VSS), U604.G5 (VSS), U604.H10 (VSS), U604.J5 (VSS), U604.K8 (VSS), U604.N2 (VSSQ), U604.N5 (VSSQ), U604.P4 (VSSQ), U604.P6 (VSSQ); also elsewhere on the board
unnamed: C604.1, U604.C2 (VDDI)
unnamed: C606.1, R602.2, U604.K5 (~RST)

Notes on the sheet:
SD1_DAT3
SD1_CLK
SD1_DAT2
SD1_CMD
